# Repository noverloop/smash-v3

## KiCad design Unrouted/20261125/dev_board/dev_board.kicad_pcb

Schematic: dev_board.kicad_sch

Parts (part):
CBAT1_1, CBAT1_2, CBAT1_3, CBAT1_4, CBAT2_1, CBAT2_2, CBAT2_3, CBAT2_4: 22uF; Capacitor_SMD_C_0805_2012Metric; MPN GRM21BR61A226ME51L
CBAT3: 1uF; Capacitor_SMD_C_0603_1608Metric; MPN C0603C105K3RACTU
CMAIN_HOLD1: 100nF; Capacitor_SMD_C_0402_1005Metric; MPN GRM155R71C104KA88D
COUT1_1, COUT1_2: 10uF; Capacitor_SMD_C_0603_1608Metric; MPN CL10A106KP8NNNC
COUT3: 100nF; Capacitor_SMD_C_0402_1005Metric; MPN GRM155R71C104KA88D
C_ACTIVATE_COMP1: 220nF; Capacitor_SMD_C_0603_1608Metric; MPN C0603C224K5RACTU
C_ACTIVATE_IN_1, C_ACTIVATE_IN_2, C_ACTIVATE_IN_3, C_ACTIVATE_IN_4, C_ACTIVATE_IN_5: 2.2uF; Capacitor_SMD_C_0603_1608Metric; MPN C0603C225K8RACTU
C_ACTIVATE_OUT_1, C_ACTIVATE_OUT_2, C_ACTIVATE_OUT_3: 4.7uF; Capacitor_SMD_C_1206_3216Metric; MPN GRM31CC72A475KE11L
C_ACTIVATE_SS1: 47nF; Capacitor_SMD_C_0402_1005Metric; MPN GRM155R71E473KA88D
C_ANTSW_S1_VDD1: 100nF; Capacitor_SMD_C_0402_1005Metric; MPN GRM155R71C104KA88D
C_ANT_S1_DCBLK1, C_ANT_S4_MATCH1: 0.8pF; Capacitor_SMD_C_0402_1005Metric; MPN GJM1555C1HR80BB01D
C_ANT_S1_SHUNT1: 0.5pF; Capacitor_SMD_C_0402_1005Metric; MPN GJM1555C1HR50BB01D
C_AON_IN1: 1uF; Capacitor_SMD_C_0603_1608Metric; MPN C0603C105K3RACTU
C_AON_OUT1: 1uF; Capacitor_SMD_C_0603_1608Metric; MPN C0603C105K3RACTU
C_AWR12_FF1, C_AWR13_FF1, C_AWR18_FF1: 120pF; Capacitor_SMD_C_0402_1005Metric; MPN 04025A121JAT2A
C_AWR_1V2_1_1, C_AWR_1V2_1_2, C_AWR_1V3_1_1, C_AWR_1V3_1_2, C_AWR_1V3_PF_1, C_AWR_1V3_PF_2, C_AWR_1V8_1_1, C_AWR_1V8_1_2, C_AWR_1V8_PF_1, C_AWR_1V8_PF_2: 10uF; Capacitor_SMD_C_0603_1608Metric; MPN CL10A106KP8NNNC
C_AWR_1V2_2, C_AWR_1V3_2, C_AWR_1V8_2: 100nF; Capacitor_SMD_C_0402_1005Metric; MPN GRM155R71C104KA88D
C_AWR_14APLL1, C_AWR_14SYNTH1: 1uF; Capacitor_SMD_C_0603_1608Metric; MPN C0603C105K3RACTU
C_AWR_BUCK_IN1_1, C_AWR_BUCK_IN1_2, C_AWR_BUCK_IN1_3, C_AWR_BUCK_IN1_4, C_AWR_BUCK_IN1_5, C_AWR_BUCK_IN3_1, C_AWR_BUCK_IN3_2, C_AWR_BUCK_IN3_3, C_AWR_BUCK_IN3_4, C_AWR_BUCK_IN3_5: 2.2uF; Capacitor_SMD_C_0603_1608Metric; MPN C0603C225K8RACTU
C_AWR_BUCK_IN2: 100nF; Capacitor_SMD_C_0402_1005Metric; MPN GRM155R71C104KA88D
C_AWR_FLASH_VCC1: 100nF; Capacitor_SMD_C_0402_1005Metric; MPN GRM155R71C104KA88D
C_AWR_NRST1: 100nF; Capacitor_SMD_C_0402_1005Metric; MPN GRM155R71C104KA88D
C_AWR_OSC_VDD1: 100nF; Capacitor_SMD_C_0402_1005Metric; MPN GRM155R71C104KA88D
C_AWR_VBGAP1: 220nF; Capacitor_SMD_C_0603_1608Metric; MPN C0603C224K5RACTU
C_AWR_VIOIN1, C_AWR_VIOIN2: 100nF; Capacitor_SMD_C_0402_1005Metric; MPN GRM155R71C104KA88D
C_AWR_VOUT_PA1: 220nF; Capacitor_SMD_C_0603_1608Metric; MPN C0603C224K5RACTU
C_AWR_VOUT_PA_BULK_1, C_AWR_VOUT_PA_BULK_2, C_AWR_VOUT_PA_BULK_3, C_AWR_VOUT_PA_BULK_4, C_AWR_VOUT_PA_BULK_5: 2.2uF; Capacitor_SMD_C_0603_1608Metric; MPN C0603C225K8RACTU
C_BAT_BULK1, C_BAT_BULK2, C_BAT_BULK3, C_BAT_BULK4, C_BAT_BULK5, C_BAT_BULK6: 22uF; Capacitor_SMD_C_0805_2012Metric; MPN GRM21BR61A226ME51L
C_BAT_SENSE1: 100nF; Capacitor_SMD_C_0402_1005Metric; MPN GRM155R71C104KA88D
C_BLE_DCBLK1: 100pF; Capacitor_SMD_C_0402_1005Metric; MPN 04025A101JAT2A
C_BOOST_CAP1: 100nF; Capacitor_SMD_C_0402_1005Metric; MPN GRM155R71C104KA88D
C_BOOST_COMP1: 1.5nF; Capacitor_SMD_C_0402_1005Metric; MPN C0402C152K3RACTU
C_BOOST_COMP_F1: 390pF; Capacitor_SMD_C_0603_1608Metric; MPN C0603C391J5GACTU
C_BOOST_IN_1, C_BOOST_IN_2, C_BOOST_IN_3, C_BOOST_IN_4, C_BOOST_IN_5: 2.2uF; Capacitor_SMD_C_0603_1608Metric; MPN C0603C225K8RACTU
C_BOOST_OUT1_1, C_BOOST_OUT1_2: 22uF; Capacitor_SMD_C_0805_2012Metric; MPN GRM21BR61E226ME44L
C_BOOST_OUT2_1, C_BOOST_OUT2_2, C_BOOST_OUT2_3, C_BOOST_OUT2_4, C_BOOST_OUT2_5: 2.2uF; Capacitor_SMD_C_0603_1608Metric; MPN C0603C225K8RACTU
C_BOOST_OUT3: 100nF; Capacitor_SMD_C_0402_1005Metric; MPN GRM155R71C104KA88D
C_BOOST_PL1: 47pF; Capacitor_SMD_C_0402_1005Metric; MPN C0402C470J5GACTU
C_BOOST_VCC_1, C_BOOST_VCC_2: 2.2uF; Capacitor_SMD_C_0603_1608Metric; MPN C0603C225K8RACTU
C_CAM_BUCK_IN1: 10uF/LV; Capacitor_SMD_C_0603_1608Metric; MPN CL10A106KP8NNNC
C_CAM_BUCK_OUT_1, C_CAM_BUCK_OUT_2: 10uF; Capacitor_SMD_C_0603_1608Metric; MPN CL10A106KP8NNNC
C_CAM_CPNEG1: 10uF/LV; Capacitor_SMD_C_0603_1608Metric; MPN CL10A106KP8NNNC
C_CAM_CPPOS1: 1uF; Capacitor_SMD_C_0603_1608Metric; MPN C0603C105K3RACTU
C_CAM_EXTCLK_VDD1: 100nF; Capacitor_SMD_C_0402_1005Metric; MPN GRM155R71C104KA88D
C_CAM_LDO2V4: 470nF; Capacitor_SMD_C_0603_1608Metric; MPN C0603C474K3RACTU
C_CAM_LDO_VAA_IN1: 1uF; Capacitor_SMD_C_0603_1608Metric; MPN C0603C105K3RACTU
C_CAM_LDO_VAA_OUT_1, C_CAM_LDO_VAA_OUT_2: 2.2uF; Capacitor_SMD_C_0603_1608Metric; MPN C0603C225K8RACTU
C_CAM_VAA_1: 100nF; Capacitor_SMD_C_0402_1005Metric; MPN GRM155R71C104KA88D
C_CAM_VAA_BULK1: 10uF/LV; Capacitor_SMD_C_0603_1608Metric; MPN CL10A106KP8NNNC
C_CAM_VCORE_1: 470nF; Capacitor_SMD_C_0603_1608Metric; MPN C0603C474K3RACTU
C_CAM_VCORE_BULK1: 10uF/LV; Capacitor_SMD_C_0603_1608Metric; MPN CL10A106KP8NNNC
C_CAM_VCORE_FF1: 120pF; Capacitor_SMD_C_0402_1005Metric; MPN 04025A121JAT2A
C_CAM_VDDIO_1: 1uF; Capacitor_SMD_C_0603_1608Metric; MPN C0603C105K3RACTU
C_CAM_VRT_1, C_CAM_VRT_2: 2.2uF; Capacitor_SMD_C_0603_1608Metric; MPN C0603C225K8RACTU
C_CAN_GW1: 100nF; Capacitor_SMD_C_0402_1005Metric; MPN GRM155R71C104KA88D
C_CAN_GW_VIO1: 100nF; Capacitor_SMD_C_0402_1005Metric; MPN GRM155R71C104KA88D
C_COMP_PZ1: 100nF; Capacitor_SMD_C_0402_1005Metric; MPN GRM155R71C104KA88D
C_DDR_BULK1_1, C_DDR_BULK1_2, C_DDR_BULK1_3, C_DDR_BULK1_4, C_DDR_BULK1_5, C_DDR_BULK2_1, C_DDR_BULK2_2, C_DDR_BULK2_3, C_DDR_BULK2_4, C_DDR_BULK2_5: 2.2uF; Capacitor_SMD_C_0603_1608Metric; MPN C0603C225K8RACTU
C_DDR_VDD1, C_DDR_VDD2, C_DDR_VDD3, C_DDR_VDD4, C_DDR_VDD5, C_DDR_VDD6: 100nF; Capacitor_SMD_C_0402_1005Metric; MPN GRM155R71C104KA88D
C_DDR_VREFCA1: 100nF; Capacitor_SMD_C_0402_1005Metric; MPN GRM155R71C104KA88D
C_DDR_VREFDQ1: 100nF; Capacitor_SMD_C_0402_1005Metric; MPN GRM155R71C104KA88D
C_DEV_BENCH1: 47uF; Capacitor_Tantalum_SMD_CP_EIA-7343-15_Kemet-W; MPN T528W 47uF (7343-15 thinnest variant)
C_DEV_BUSSW0, C_DEV_BUSSW1, C_DEV_BUSSW2, C_DEV_BUSSW3: 100nF; Capacitor_SMD_C_0402_1005Metric; MPN GRM155R71C104KA88D
C_DEV_CAN_VCC1: 100nF; Capacitor_SMD_C_0402_1005Metric; MPN GRM155R71C104KA88D
C_DEV_CAN_VIO1: 100nF; Capacitor_SMD_C_0402_1005Metric; MPN GRM155R71C104KA88D
C_DEV_FLATSW0, C_DEV_FLATSW1, C_DEV_FLATSW2, C_DEV_FLATSW3: 100nF; Capacitor_SMD_C_0402_1005Metric; MPN GRM155R71C104KA88D
C_DEV_FLAT_PWR_SS1: 22nF; Capacitor_SMD_C_0402_1005Metric; MPN C0402C223K3RACTU
C_DEV_INA1: 100nF; Capacitor_SMD_C_0402_1005Metric; MPN GRM155R71C104KA88D
C_DEV_ISENSE1: 100nF; Capacitor_SMD_C_0402_1005Metric; MPN GRM155R71C104KA88D
C_DEV_LDO_IN1: 1uF; Capacitor_SMD_C_0603_1608Metric; MPN C0603C105K3RACTU
C_DEV_LDO_OUT_1, C_DEV_LDO_OUT_2, C_DEV_LDO_OUT_3, C_DEV_LDO_OUT_4, C_DEV_LDO_OUT_5: 2.2uF; Capacitor_SMD_C_0603_1608Metric; MPN C0603C225K8RACTU
C_DEV_MCU_0, C_DEV_MCU_1, C_DEV_MCU_2, C_DEV_MCU_3: 100nF; Capacitor_SMD_C_0402_1005Metric; MPN GRM155R71C104KA88D
C_DEV_MCU_BULK_1, C_DEV_MCU_BULK_2: 2.2uF; Capacitor_SMD_C_0603_1608Metric; MPN C0603C225K8RACTU
C_DEV_MCU_NRST1: 100nF; Capacitor_SMD_C_0402_1005Metric; MPN GRM155R71C104KA88D
C_DEV_MCU_VCAP_1, C_DEV_MCU_VCAP_2: 2.2uF; Capacitor_SMD_C_0603_1608Metric; MPN C0603C225K8RACTU
C_DEV_MON1_0, C_DEV_MON1_1, C_DEV_MON1_2, C_DEV_MON1_3, C_DEV_MON1_4, C_DEV_MON1_5, C_DEV_MON1_6, C_DEV_MON1_7, C_DEV_MON2_0, C_DEV_MON2_1, C_DEV_MON2_2, C_DEV_MON2_3, C_DEV_MON2_4, C_DEV_MON2_5, C_DEV_MON2_6, C_DEV_MON2_7, C_DEV_MON3_0, C_DEV_MON3_1, C_DEV_MON3_2, C_DEV_MON3_3, C_DEV_MON3_4: 10nF; Capacitor_SMD_C_0402_1005Metric; MPN C0402C103K3RACTU
C_DEV_MON1_AVDD1, C_DEV_MON1_DECAP1, C_DEV_MON1_DVDD1, C_DEV_MON2_AVDD1, C_DEV_MON2_DECAP1, C_DEV_MON2_DVDD1, C_DEV_MON3_AVDD1, C_DEV_MON3_DECAP1, C_DEV_MON3_DVDD1: 1uF; Capacitor_SMD_C_0603_1608Metric; MPN C0603C105K3RACTU
C_DEV_OVP_FLAT_IN1: 1nF; Capacitor_SMD_C_0402_1005Metric; MPN C0402C102K3RACTU
C_DEV_OVP_FLAT_VCC1: 100nF; Capacitor_SMD_C_0402_1005Metric; MPN GRM155R71C104KA88D
C_DEV_OVP_IN1: 1nF; Capacitor_SMD_C_0402_1005Metric; MPN C0402C102K3RACTU
C_DEV_OVP_VCC1: 100nF; Capacitor_SMD_C_0402_1005Metric; MPN GRM155R71C104KA88D
C_DEV_TWR_PWR_SS1: 22nF; Capacitor_SMD_C_0402_1005Metric; MPN C0402C223K3RACTU
C_FIN1_VM1, C_FIN2_VM1, C_FIN3_VM1, C_FIN4_VM1: 100nF; Capacitor_SMD_C_0402_1005Metric; MPN GRM155R71C104KA88D
C_FIN_MCU_BULK1: 1uF; Capacitor_SMD_C_0603_1608Metric; MPN C0603C105K3RACTU
C_FIN_MCU_NRST1: 100nF; Capacitor_SMD_C_0402_1005Metric; MPN GRM155R71C104KA88D
C_FIN_MCU_SMPS_IN_1, C_FIN_MCU_SMPS_IN_2: 2.2uF; Capacitor_SMD_C_0603_1608Metric; MPN C0603C225K8RACTU
C_FIN_MCU_VDD1, C_FIN_MCU_VDD2: 100nF; Capacitor_SMD_C_0402_1005Metric; MPN GRM155R71C104KA88D
C_FIN_MCU_VDD11_1, C_FIN_MCU_VDD11_2: 2.2uF; Capacitor_SMD_C_0603_1608Metric; MPN C0603C225K8RACTU
C_FIN_MCU_VDDA1: 100nF; Capacitor_SMD_C_0402_1005Metric; MPN GRM155R71C104KA88D
C_FIN_VM_BULK_1, C_FIN_VM_BULK_2, C_FIN_VM_BULK_3, C_FIN_VM_BULK_4, C_FIN_VM_BULK_5: 2.2uF; Capacitor_SMD_C_0603_1608Metric; MPN C0603C225K8RACTU
C_HACC1: 100nF; Capacitor_SMD_C_0402_1005Metric; MPN GRM155R71C104KA88D
C_HACC2_1, C_HACC2_2, C_HACC2_3, C_HACC2_4, C_HACC2_5: 2.2uF; Capacitor_SMD_C_0603_1608Metric; MPN C0603C225K8RACTU
C_HEALTH_COIL_1, C_HEALTH_COIL_2, C_HEALTH_COIL_3, C_HEALTH_COIL_4, C_HEALTH_COIL_5: 2.2uF; Capacitor_SMD_C_0603_1608Metric; MPN C0603C225K8RACTU
C_IMU1_1, C_IMU2_1, C_IMU3_1: 100nF; Capacitor_SMD_C_0402_1005Metric; MPN GRM155R71C104KA88D
C_IMU1_2, C_IMU2_2, C_IMU3_2: 2.2uF; Capacitor_SMD_C_0603_1608Metric; MPN C0603C225K8RACTU
C_IMU1_3, C_IMU2_3, C_IMU3_3: 10nF; Capacitor_SMD_C_0402_1005Metric; MPN C0402C103K3RACTU
C_IR_TX1: 1uF; Capacitor_SMD_C_0603_1608Metric; MPN C0603C105K3RACTU
C_IR_TX_C1: 1uF; Capacitor_SMD_C_0603_1608Metric; MPN C0603C105K3RACTU
C_IR_TX_Q1: 1uF; Capacitor_SMD_C_0603_1608Metric; MPN C0603C105K3RACTU
C_IR_WAKE1: 10nF; Capacitor_SMD_C_0402_1005Metric; MPN C0402C103K3RACTU
C_J_HALL_FIN_VCC1: 100nF; Capacitor_SMD_C_0402_1005Metric; MPN GRM155R71C104KA88D
C_LR_BULK_1, C_LR_BULK_2: 2.2uF; Capacitor_SMD_C_0603_1608Metric; MPN C0603C225K8RACTU
C_LR_DTC1_VDD1, C_LR_DTC2_VDD1: 100nF; Capacitor_SMD_C_0402_1005Metric; MPN GRM155R71C104KA88D
C_LR_HF_ANTBLK1: 100pF; Capacitor_SMD_C_0402_1005Metric; MPN 04025A101JAT2A
C_LR_HF_RX1: 0.8pF; Capacitor_SMD_C_0402_1005Metric; MPN GJM1555C1HR80BB01D
C_LR_HF_RXBLK1: 100pF; Capacitor_SMD_C_0402_1005Metric; MPN 04025A101JAT2A
C_LR_HF_TX1: 1.2pF; Capacitor_SMD_C_0402_1005Metric; MPN GJM1555C1H1R2BB01D
C_LR_HF_TX2: 1.0pF; Capacitor_SMD_C_0402_1005Metric; MPN GJM1555C1H1R0BB01D
C_LR_HF_TXBLK1: 100pF; Capacitor_SMD_C_0402_1005Metric; MPN 04025A101JAT2A
C_LR_IFSW_VDD1: 100nF; Capacitor_SMD_C_0402_1005Metric; MPN GRM155R71C104KA88D
C_LR_SW_HF_VDD1: 100nF; Capacitor_SMD_C_0402_1005Metric; MPN GRM155R71C104KA88D
C_LR_TCXO_AC1: 10pF; Capacitor_SMD_C_0402_1005Metric; MPN 04025A100JAT2A
C_LR_TCXO_MEMS1: 100nF; Capacitor_SMD_C_0402_1005Metric; MPN GRM155R71C104KA88D
C_LR_TCXO_MEMS2: 1uF; Capacitor_SMD_C_0603_1608Metric; MPN C0603C105K3RACTU
C_LR_VBAT1: 100nF; Capacitor_SMD_C_0402_1005Metric; MPN GRM155R71C104KA88D
C_LR_VDCC1, C_LR_VDCC2: 1uF; Capacitor_SMD_C_0603_1608Metric; MPN C0603C105K3RACTU
C_LR_VPAX1, C_LR_VPAX2: 2.2uF; Capacitor_SMD_C_0603_1608Metric; MPN C0603C225K8RACTU
C_LR_VRPA1: 1nF; Capacitor_SMD_C_0402_1005Metric; MPN C0402C102K3RACTU
C_LR_VTCXO1: 100nF; Capacitor_SMD_C_0402_1005Metric; MPN GRM155R71C104KA88D
C_MAG1: 100nF; Capacitor_SMD_C_0402_1005Metric; MPN GRM155R71C104KA88D
C_MAG2: 1uF; Capacitor_SMD_C_0603_1608Metric; MPN C0603C105K3RACTU
C_MAG_C1: 2.2uF; Capacitor_SMD_C_0603_1608Metric; MPN C0603C225K8RACTU
C_MAG_LDO_IN1: 1uF; Capacitor_SMD_C_0603_1608Metric; MPN C0603C105K3RACTU
C_MAG_LDO_OUT1: 1uF; Capacitor_SMD_C_0603_1608Metric; MPN C0603C105K3RACTU
C_MAG_SHELF1: 100nF; Capacitor_SMD_C_0402_1005Metric; MPN GRM155R71C104KA88D
C_MAG_WAKE1: 100nF; Capacitor_SMD_C_0402_1005Metric; MPN GRM155R71C104KA88D
C_MPU_0V82_1, C_MPU_0V82_2, C_MPU_5V2, C_MPU_18AON1, C_MPU_18A_1, C_MPU_18A_2, C_MPU_33b1: 100nF; Capacitor_SMD_C_0402_1005Metric; MPN GRM155R71C104KA88D
C_MPU_0V82_BULK1, C_MPU_5V_1, C_MPU_5V_2, C_MPU_5V_3, C_MPU_5V_4, C_MPU_5V_5, C_MPU_33_1, C_MPU_33_2, C_MPU_33_3, C_MPU_33_4, C_MPU_33_5: 2.2uF; Capacitor_SMD_C_0603_1608Metric; MPN C0603C225K8RACTU
C_MPU_HSE_VDD1: 100nF; Capacitor_SMD_C_0402_1005Metric; MPN GRM155R71C104KA88D
C_MPU_LSE_VDD1: 100nF; Capacitor_SMD_C_0402_1005Metric; MPN GRM155R71C104KA88D
C_MPU_NRST1: 100nF; Capacitor_SMD_C_0402_1005Metric; MPN GRM155R71C104KA88D
C_MPU_QDDR_1, C_MPU_QDDR_2: 100nF; Capacitor_SMD_C_0402_1005Metric; MPN GRM155R71C104KA88D
C_MPU_V08CAP1: 2.2uF; Capacitor_SMD_C_0603_1608Metric; MPN C0603C225K8RACTU
C_NAND_A_BULK1: 1uF; Capacitor_SMD_C_0603_1608Metric; MPN C0603C105K3RACTU
C_NAND_A_VCC1: 100nF; Capacitor_SMD_C_0402_1005Metric; MPN GRM155R71C104KA88D
C_NAND_B_BULK1: 1uF; Capacitor_SMD_C_0603_1608Metric; MPN C0603C105K3RACTU
C_NAND_B_VCC1: 100nF; Capacitor_SMD_C_0402_1005Metric; MPN GRM155R71C104KA88D
C_PMIC_0V9_1_1, C_PMIC_0V9_1_2, C_PMIC_0V82_1_1, C_PMIC_0V82_1_2, C_PMIC_1V8_1_1, C_PMIC_1V8_1_2, C_PMIC_3V3_1_1, C_PMIC_3V3_1_2: 10uF; Capacitor_SMD_C_0603_1608Metric; MPN CL10A106KP8NNNC
C_PMIC_0V9_2, C_PMIC_0V82_2, C_PMIC_1V8_2, C_PMIC_1V35_2, C_PMIC_2V8_2, C_PMIC_3V3_2: 100nF; Capacitor_SMD_C_0402_1005Metric; MPN GRM155R71C104KA88D
C_PMIC_1V35_1_1, C_PMIC_1V35_1_2, C_PMIC_1V35_1_3, C_PMIC_1V35_1_4, C_PMIC_1V35_1_5, C_PMIC_2V8_1_1, C_PMIC_2V8_1_2, C_PMIC_5V_FILT_1, C_PMIC_5V_FILT_2, C_PMIC_5V_FILT_3, C_PMIC_5V_FILT_4, C_PMIC_5V_FILT_5: 2.2uF; Capacitor_SMD_C_0603_1608Metric; MPN C0603C225K8RACTU
C_PMIC_INTLDO_1, C_PMIC_INTLDO_2: 2.2uF; Capacitor_SMD_C_0603_1608Metric; MPN C0603C225K8RACTU
C_PMIC_LDO1_1, C_PMIC_LDO1_2, C_PMIC_LDO2_1, C_PMIC_LDO2_2, C_PMIC_LDO4_1, C_PMIC_LDO4_2: 2.2uF; Capacitor_SMD_C_0603_1608Metric; MPN C0603C225K8RACTU
C_PMIC_LDO6, C_PMIC_LDO7, C_PMIC_LDO8: 100nF; Capacitor_SMD_C_0402_1005Metric; MPN GRM155R71C104KA88D
C_PMIC_VIN1: 22uF; Capacitor_Tantalum_SMD_CP_EIA-3528-12_Kemet-T; MPN T491T226K010AT
C_PMIC_VIN2: 100nF; Capacitor_SMD_C_0402_1005Metric; MPN GRM155R71C104KA88D
C_PMIC_VIN3, C_PMIC_VIN4, C_PMIC_VIN5, C_PMIC_VIN6: 2.2uF; Capacitor_SMD_C_0603_1608Metric; MPN C0603C225K8RACTU
C_PMIC_VREFDDR1: 1uF; Capacitor_SMD_C_0402_1005Metric; MPN GRM155R61E105KA12D
C_PWR_FF1: 120pF; Capacitor_SMD_C_0402_1005Metric; MPN 04025A121JAT2A
C_PWR_IN_1, C_PWR_IN_2, C_PWR_IN_3, C_PWR_IN_4, C_PWR_IN_5: 2.2uF; Capacitor_SMD_C_0603_1608Metric; MPN C0603C225K8RACTU
C_PZ_TX1: 10nF; Capacitor_SMD_C_0402_1005Metric; MPN C0402C103K3RACTU
C_QPD_VREF1: 1uF; Capacitor_SMD_C_0603_1608Metric; MPN C0603C105K3RACTU
C_QPD_VREF2: 100nF; Capacitor_SMD_C_0402_1005Metric; MPN GRM155R71C104KA88D
C_TIA_A1: 8.2pF; Capacitor_SMD_C_0603_1608Metric; MPN C0603C829C5GACTU
C_TIA_A_PWR1: 100nF; Capacitor_SMD_C_0402_1005Metric; MPN GRM155R71C104KA88D
C_TIA_B1: 8.2pF; Capacitor_SMD_C_0603_1608Metric; MPN C0603C829C5GACTU
C_TIA_B_PWR1: 100nF; Capacitor_SMD_C_0402_1005Metric; MPN GRM155R71C104KA88D
C_TIA_C1: 8.2pF; Capacitor_SMD_C_0603_1608Metric; MPN C0603C829C5GACTU
C_TIA_C_PWR1: 100nF; Capacitor_SMD_C_0402_1005Metric; MPN GRM155R71C104KA88D
C_TIA_D1: 8.2pF; Capacitor_SMD_C_0603_1608Metric; MPN C0603C829C5GACTU
C_TIA_D_PWR1: 100nF; Capacitor_SMD_C_0402_1005Metric; MPN GRM155R71C104KA88D
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
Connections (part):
3V3: COUT1_1.1, COUT1_2.1, COUT3.1, C_PWR_FF1.1, C_TMP1.1, J_CAST_power_board1.3 (3V3@27.068deg), L_PWR1.2, R_DEV_MON2_2.1, R_DEV_SH_3V3_ACT1.2, R_DEV_SH_3V3_QPD1.2, R_DEV_SH_3V3_RADAR1.2, R_DEV_SH_3V3_WAKE1.2, R_PWR_FB1.1, S_DEV_LAUNCH1.2 (A), TP_DEV_SH_3V3_ACT_B1.1, TP_DEV_SH_3V3_QPD_B1.1, TP_DEV_SH_3V3_RADAR_B1.1, TP_DEV_SH_3V3_WAKE_B1.1, U_PMIC1.29 (VIO), U_TMP1.6 (A1), U_TMP1.8 (VDD)
3V3_AON: C_AON_OUT1.1, C_COMP_PZ1.1, C_MAG_WAKE1.1, C_WBA_BULK_1.1, C_WBA_BULK_2.1, C_WBA_BULK_3.1, C_WBA_BULK_4.1, C_WBA_BULK_5.1, C_WBA_SMPS_IN_1.1, C_WBA_SMPS_IN_2.1, C_WBA_SMPS_IN_3.1, C_WBA_SMPS_IN_4.1, C_WBA_SMPS_IN_5.1, C_WBA_VDD1.1, C_WBA_VDD2.1, C_WBA_VDD3.1, C_WBA_VDD4.1, C_WBA_VDDA1.1, C_WBA_VDDANA1.1, C_WBA_VDDA_1U1.1, C_WBA_VDDRF1.1, C_WBA_VDDRFPA1.1, C_WBA_VDDSMPS1.1, J_CAST_activation_interface1.22 (3V3_AON@78.496deg), J_CAST_aft_end_board1.12 (3V3_AON@78.25deg), J_CAST_wakeup_board1.15 (3V3_AON@78.496deg), RPU_IR_WAKE1.1, RPU_MAG_WAKE1.1, R_DEV_MON2_3.1, R_VDD_SENSE1.2, R_WBA_NRST1.1, U_AON_LDO1.1 (VOUT), U_COMP_PZ1.B1 (VCC), U_MAG_WAKE1.1 (VCC), U_WBA1.A4 (VDD_RFPA), U_WBA1.A6 (VDDRF), U_WBA1.B1 (VDD_SMPS), U_WBA1.B6 (VDD_ANA), U_WBA1.C6 (VDD_1), U_WBA1.D5 (VDD_2), U_WBA1.E4 (VDD_3), U_WBA1.F1 (VDDA), U_WBA1.F5 (VDD_4)
3V3__ACT: C_FIN_MCU_BULK1.1, C_FIN_MCU_SMPS_IN_1.1, C_FIN_MCU_SMPS_IN_2.1, C_FIN_MCU_VDD1.1, C_FIN_MCU_VDD2.1, C_FIN_MCU_VDDA1.1, C_HACC1.1, C_HACC2_1.1, C_HACC2_2.1, C_HACC2_3.1, C_HACC2_4.1, C_HACC2_5.1, C_IMU1_1.1, C_IMU1_2.1, C_IMU1_3.1, C_IMU2_1.1, C_IMU2_2.1, C_IMU2_3.1, C_IMU3_1.1, C_IMU3_2.1, C_IMU3_3.1, C_J_HALL_FIN_VCC1.1, C_MAG2.1, C_MAG_LDO_IN1.1, J_CAST_activation_interface1.5 (3V3@27.068deg), J_HALL_FIN_VCC1.1, R_DEV_SH_3V3_ACT1.1, R_FIN_MCU_NRST1.1, R_FIN_SPI_CS_PU1.1, R_HALL_VIN1.1, R_IMU1_SCX_PU1.1, R_IMU1_SDX_PU1.1, R_IMU2_SCX_PU1.1, R_IMU2_SDX_PU1.1, R_IMU3_SCX_PU1.1, R_IMU3_SDX_PU1.1, R_J_HALL_FIN_PU1.1, TP_DEV_SH_3V3_ACT_T1.1, U_FIN1.16 (MODE), U_FIN2.16 (MODE), U_FIN3.16 (MODE), U_FIN4.16 (MODE), U_FIN_MCU1.A1 (VDD_1), U_FIN_MCU1.A8 (VDD_2), U_FIN_MCU1.B1 (VBAT), U_FIN_MCU1.B8 (VDDUSB), U_FIN_MCU1.G1 (VDDA), U_FIN_MCU1.H1 (VDD_3), U_FIN_MCU1.H6 (VDDSMPS), U_FIN_MCU1.H8 (VDD_4), U_HACC1.1 (VDD_IO), U_HACC1.8 (CS), U_HACC1.14 (VDD), U_HACC1.15 (RESERVED_2), U_IMU1.5 (VDDIO), U_IMU1.8 (VDD), U_IMU1.12 (CS), U_IMU2.5 (VDDIO), U_IMU2.8 (VDD), U_IMU2.12 (CS), U_IMU3.1 (SDO/SA0), U_IMU3.5 (VDDIO), U_IMU3.8 (VDD), U_IMU3.12 (CS), U_MAG1.B3 (VDDIO), U_MAG_LDO1.3 (ON/OFF), U_MAG_LDO1.4 (VIN)
3V3__QPD: C_TIA_A_PWR1.1, C_TIA_B_PWR1.1, C_TIA_C_PWR1.1, C_TIA_D_PWR1.1, J_CAST_qpd_module1.2 (3V3@27.068deg), R_DEV_SH_3V3_QPD1.1, R_QPD_VREF_H1.1, TP_DEV_SH_3V3_QPD_T1.1, U_TIA_A1.5 (V+), U_TIA_B1.5 (V+), U_TIA_C1.5 (V+), U_TIA_D1.5 (V+)
3V3__RADAR: J_CAST_radar_module1.3 (3V3@27.068deg), R_DEV_SH_3V3_RADAR1.1, TP_DEV_SH_3V3_RADAR_T1.1
3V3__WAKE: C_ANTSW_S1_VDD1.1, C_LR_DTC1_VDD1.1, C_LR_DTC2_VDD1.1, C_LR_IFSW_VDD1.1, C_LR_SW_HF_VDD1.1, C_WBA_HSE_VDD1.1, C_XV_MIX_VCC1.1, C_XV_MIX_VCC2.1, C_XV_TR1_VDD1.1, C_XV_TR2_VDD1.1, FB_LR_VBAT1.1, FB_XV_LO1.1, J_CAST_wakeup_board1.3 (3V3@27.068deg), Q_LR_TCXO_SW1.2 (S), RPU_I2C2_SCL1.1, RPU_I2C2_SDA1.1, RPU_I2C3_SCL1.1, RPU_I2C3_SDA1.1, RPU_SCL_EXT1.1, RPU_SDA_EXT1.1, R_DEV_SH_3V3_WAKE1.1, R_LR_NSS_PU1.1, R_LR_TCXO_SW_PU1.1, R_XV_LNA_VDD1.1, TP_3V3.1, TP_DEV_SH_3V3_WAKE_T1.1, U_ANTSW_S1.4 (VDD), U_LR_DTC1.4 (VDD), U_LR_DTC2.4 (VDD), U_LR_IFSW1.4 (VDD), U_LR_SW_HF1.4 (VDD), U_XV_MIX1.9 (VCC), U_XV_TR1.4 (VDD), U_XV_TR2.4 (VDD), Y_WBA_HSE1.1 (STANDBY#), Y_WBA_HSE1.4 (VDD)
ACTIVATE_BOOST_EN: J_CAST_companion_compute1.60 (ACTIVATE_BOOST_EN@273.383deg), J_CAST_power_board1.27 (ACTIVATE_BOOST_EN@273.383deg), R_ACTIVATE_EN_PD1.1, TP_DEV_DBG_ACTIVATE_BOOST_EN1.1, U_ACTIVATE_BOOST1.4 (EN), U_MPU1.F5 (PG10)
ACTIVATE_COMP: R_ACTIVATE_COMP1.1, U_ACTIVATE_BOOST1.8 (COMP)
ACTIVATE_COMP_C: C_ACTIVATE_COMP1.1, R_ACTIVATE_COMP1.2
ACTIVATE_CONFIRM: J_CAST_activation_interface1.62 (ACTIVATE_CONFIRM@322.105deg), J_CAST_companion_compute1.70 (ACTIVATE_CONFIRM@322.105deg), R_ACTIVATE_MON1.2, R_ACTIVATE_MON2.1, R_ACT_CONFIRM_PAD1.2, U_MPU1.C10 (PD9)
ACTIVATE_CONFIRM_PAD: J_CAST_activation_interface1.56 (ACTIVATE_CONFIRM_PAD@305.865deg), J_CAST_aft_end_board1.31 (ACTIVATE_CONFIRM_PAD@264.25deg), R_ACT_CONFIRM_PAD1.1, TP_ACT_CONFIRM1.1, U_ESD_AFT7.3 (IO2)
ACTIVATE_FB: R_ACTIVATE_FB1.2, R_ACTIVATE_FB2.1, U_ACTIVATE_BOOST1.9 (FB)
ACTIVATE_FREQ: R_ACTIVATE_FREQ1.1, U_ACTIVATE_BOOST1.10 (FREQ)
ACTIVATE_HV: C_ACTIVATE_OUT_1.1, C_ACTIVATE_OUT_2.1, C_ACTIVATE_OUT_3.1, D_ACTIVATE1.1 (K), J_CAST_activation_interface1.55 (ACTIVATE_HV@303.158deg), J_CAST_power_board1.31 (ACTIVATE_HV@303.158deg), Q_PARACHUTE_CUTTER_ACTIVATE1.4 (S_1), Q_PARACHUTE_CUTTER_ACTIVATE1.8 (S_2), R_ACTIVATE_BLEED1.1, R_ACTIVATE_FB1.1, R_ACTIVATE_MON1.1, R_DEV_LED_HV1.1, R_DEV_MON2_6.1, R_PARACHUTE_CUTTER_ACTIVATE_H1.1, TP_DEV_DBG_ACTIVATE_HV1.1
ACTIVATE_SS: C_ACTIVATE_SS1.1, U_ACTIVATE_BOOST1.5 (SS)
ACTIVATE_SW: D_ACTIVATE1.2 (A), L_ACTIVATE1.1, U_ACTIVATE_BOOST1.1 (SW_1), U_ACTIVATE_BOOST1.2 (SW_2)
ACT_COL_0: D_ACT_COL0_TVS1.1 (K), J_CAST_activation_interface1.13 (ACT_COL_0@54.135deg), J_CAST_aft_end_board1.7 (ACT_COL_0@49.25deg), P_ACT_COL_0.1, Q_ACT_COL0.3 (D)
ACT_COL_1: D_ACT_COL1_TVS1.1 (K), J_CAST_activation_interface1.15 (ACT_COL_1@59.549deg), J_CAST_aft_end_board1.8 (ACT_COL_1@52deg), P_ACT_COL_1.1, Q_ACT_COL1.3 (D)
ACT_COL_2: D_ACT_COL2_TVS1.1 (K), J_CAST_activation_interface1.53 (ACT_COL_2@297.744deg), J_CAST_aft_end_board1.30 (ACT_COL_2@261.5deg), P_ACT_COL_2.1, Q_ACT_COL2.3 (D)
ACT_COL_3: D_ACT_COL3_TVS1.1 (K), J_CAST_activation_interface1.16 (ACT_COL_3@62.256deg), J_CAST_aft_end_board1.9 (ACT_COL_3@54.75deg), P_ACT_COL_3.1, Q_ACT_COL3.3 (D)
ACT_COL_SEL_0: Q_ACT_COL0.1 (G), R_ACT_COL0_PD1.1, U_FIN_MCU1.D7 (PA8)
ACT_COL_SEL_1: Q_ACT_COL1.1 (G), R_ACT_COL1_PD1.1, U_FIN_MCU1.D6 (PA9)
ACT_COL_SEL_2: Q_ACT_COL2.1 (G), R_ACT_COL2_PD1.1, U_FIN_MCU1.D5 (PA10)
ACT_COL_SEL_3: Q_ACT_COL3.1 (G), R_ACT_COL3_PD1.1, U_FIN_MCU1.C8 (PA11)
ACT_ROW_0: D_ACT_WIRE_0.2 (A), D_ACT_WIRE_1.2 (A), D_ACT_WIRE_2.2 (A), D_ACT_WIRE_3.2 (A), J_CAST_activation_interface1.52 (ACT_ROW_0@295.038deg), J_CAST_aft_end_board1.29 (ACT_ROW_0@258.75deg), Q_ACT_ROW0.1 (D_1), Q_ACT_ROW0.2 (D_2), Q_ACT_ROW0.5 (D_3), Q_ACT_ROW0.6 (D_4), Q_ACT_ROW0.7 (D_5)
ACT_ROW_0_G: Q_ACT_ROW0.3 (G), R_ACT_ROW0_H1.2, R_ACT_ROW0_L1.1
ACT_ROW_0_GD: Q_ACT_ROW0_LS1.3 (D), R_ACT_ROW0_L1.2
ACT_ROW_1: D_ACT_WIRE_4.2 (A), D_ACT_WIRE_5.2 (A), D_ACT_WIRE_6.2 (A), D_ACT_WIRE_7.2 (A), J_CAST_activation_interface1.17 (ACT_ROW_1@64.962deg), J_CAST_aft_end_board1.10 (ACT_ROW_1@57.5deg), Q_ACT_ROW1.1 (D_1), Q_ACT_ROW1.2 (D_2), Q_ACT_ROW1.5 (D_3), Q_ACT_ROW1.6 (D_4), Q_ACT_ROW1.7 (D_5)
ACT_ROW_1_G: Q_ACT_ROW1.3 (G), R_ACT_ROW1_H1.2, R_ACT_ROW1_L1.1
ACT_ROW_1_GD: Q_ACT_ROW1_LS1.3 (D), R_ACT_ROW1_L1.2
ACT_ROW_2: D_ACT_WIRE_8.2 (A), D_ACT_WIRE_9.2 (A), D_ACT_WIRE_10.2 (A), D_ACT_WIRE_11.2 (A), J_CAST_activation_interface1.51 (ACT_ROW_2@292.331deg), J_CAST_aft_end_board1.28 (ACT_ROW_2@256deg), Q_ACT_ROW2.1 (D_1), Q_ACT_ROW2.2 (D_2), Q_ACT_ROW2.5 (D_3), Q_ACT_ROW2.6 (D_4), Q_ACT_ROW2.7 (D_5)
ACT_ROW_2_G: Q_ACT_ROW2.3 (G), R_ACT_ROW2_H1.2, R_ACT_ROW2_L1.1
ACT_ROW_2_GD: Q_ACT_ROW2_LS1.3 (D), R_ACT_ROW2_L1.2
ACT_ROW_3: D_ACT_WIRE_12.2 (A), D_ACT_WIRE_13.2 (A), D_ACT_WIRE_14.2 (A), D_ACT_WIRE_15.2 (A), J_CAST_activation_interface1.18 (ACT_ROW_3@67.669deg), J_CAST_aft_end_board1.11 (ACT_ROW_3@60.25deg), Q_ACT_ROW3.1 (D_1), Q_ACT_ROW3.2 (D_2), Q_ACT_ROW3.5 (D_3), Q_ACT_ROW3.6 (D_4), Q_ACT_ROW3.7 (D_5)
ACT_ROW_3_G: Q_ACT_ROW3.3 (G), R_ACT_ROW3_H1.2, R_ACT_ROW3_L1.1
ACT_ROW_3_GD: Q_ACT_ROW3_LS1.3 (D), R_ACT_ROW3_L1.2
ACT_ROW_SEL_0: Q_ACT_ROW0_LS1.1 (G), R_ACT_ROW0_PD1.1, U_FIN_MCU1.E2 (PC0)
ACT_ROW_SEL_1: Q_ACT_ROW1_LS1.1 (G), R_ACT_ROW1_PD1.1, U_FIN_MCU1.E3 (PC1)
ACT_ROW_SEL_2: Q_ACT_ROW2_LS1.1 (G), R_ACT_ROW2_PD1.1, U_FIN_MCU1.E4 (PC2)
ACT_ROW_SEL_3: Q_ACT_ROW3_LS1.1 (G), R_ACT_ROW3_PD1.1, U_FIN_MCU1.F2 (PC3)
ACT_WIRE_0: D_ACT_WIRE_0.1 (K), P_ACT_WIRE_0.1
ACT_WIRE_1: D_ACT_WIRE_1.1 (K), P_ACT_WIRE_1.1
ACT_WIRE_2: D_ACT_WIRE_2.1 (K), P_ACT_WIRE_2.1
ACT_WIRE_3: D_ACT_WIRE_3.1 (K), P_ACT_WIRE_3.1
ACT_WIRE_4: D_ACT_WIRE_4.1 (K), P_ACT_WIRE_4.1
ACT_WIRE_5: D_ACT_WIRE_5.1 (K), P_ACT_WIRE_5.1
ACT_WIRE_6: D_ACT_WIRE_6.1 (K), P_ACT_WIRE_6.1
ACT_WIRE_7: D_ACT_WIRE_7.1 (K), P_ACT_WIRE_7.1
ACT_WIRE_8: D_ACT_WIRE_8.1 (K), P_ACT_WIRE_8.1
ACT_WIRE_9: D_ACT_WIRE_9.1 (K), P_ACT_WIRE_9.1
ACT_WIRE_10: D_ACT_WIRE_10.1 (K), P_ACT_WIRE_10.1
ACT_WIRE_11: D_ACT_WIRE_11.1 (K), P_ACT_WIRE_11.1
ACT_WIRE_12: D_ACT_WIRE_12.1 (K), P_ACT_WIRE_12.1
ACT_WIRE_13: D_ACT_WIRE_13.1 (K), P_ACT_WIRE_13.1
ACT_WIRE_14: D_ACT_WIRE_14.1 (K), P_ACT_WIRE_14.1
ACT_WIRE_15: D_ACT_WIRE_15.1 (K), P_ACT_WIRE_15.1
ANTSW_S1_LR: R_ANTSW_S1_PD1.1, U_ANTSW_S1.6 (CTRL), U_LR1.9 (DIO9)
ANT_HF_S1: C_ANT_S1_DCBLK1.2, J_CAST_wakeup_board1.22 (ANT_HF_S1@129.4deg), J_DEV_HF_S1.3
ANT_HF_S4: C_ANT_S4_MATCH1.2, J_CAST_wakeup_board1.25 (ANT_HF_S4@154.3deg), J_DEV_HF_S4.3
ANT_S1_COM: C_ANT_S1_DCBLK1.1, C_ANT_S1_SHUNT1.1, U_ANTSW_S1.5 (RFIN)
AON_EN: DHOLD_AON1.1 (K), DHOLD_AON_MP25.1 (K), Q_AON_EN1.3 (D), R_AON_EN_PD1.1, U_AON_LDO1.3 (ON/OFF)
AON_EN_GATE: D_AON_WAKE1.2 (A), D_AON_WAKE2.2 (A), Q_AON_EN1.1 (G), Q_USB_WAKE2.3 (D), RAON_PU1.2
AWR_1V2: C_AWR12_FF1.1, C_AWR_1V2_1_1.1, C_AWR_1V2_1_2.1, C_AWR_1V2_2.1, J_CAST_radar_module1.42 (AWR_1V2@249.023deg), L_AWR_BUCK12.2, R_AWR12_FB1.1, R_DEV_MON2_7.1, TP_DEV_DBG_AWR_1V2.1, U_AWR1.A5 (VIN_SRAM_1), U_AWR1.C1 (VNWA_1), U_AWR1.E1 (VDDIN_1), U_AWR1.J1 (VDDIN_2), U_AWR1.V4 (VDDIN_3), U_AWR1.V6 (VIN_SRAM_2), U_AWR1.V7 (VNWA_2), U_AWR1.V8 (VDDIN_4), U_AWR1.V12 (VIN_SRAM_3), U_AWR1.V14 (VNWA_3), U_AWR1.V15 (VDDIN_5)
AWR_1V2_FB: C_AWR12_FF1.2, R_AWR12_FB1.2, R_AWR12_FB2.1, U_AWR_BUCK12.2 (FB)
AWR_1V2_SW: L_AWR_BUCK12.1, U_AWR_BUCK12.6 (SW)
AWR_1V3: C_AWR_1V3_PF_1.1, C_AWR_1V3_PF_2.1, FB_AWR_1V3.2, J_CAST_radar_module1.37 (AWR_1V3@216.541deg), R_DEV_MON3_0.1, TP_DEV_DBG_AWR_1V3.1, U_AWR1.H16 (VIN_13RF2_1), U_AWR1.H17 (VIN_13RF2_2), U_AWR1.H18 (VIN_13RF2_3), U_AWR1.J16 (VIN_13RF1_1), U_AWR1.J17 (VIN_13RF1_2), U_AWR1.J18 (VIN_13RF1_3)
AWR_1V3_BK: C_AWR13_FF1.1, C_AWR_1V3_1_1.1, C_AWR_1V3_1_2.1, C_AWR_1V3_2.1, FB_AWR_1V3.1, L_AWR_BUCK13.2, R_AWR13_FB1.1
AWR_1V3_FB: C_AWR13_FF1.2, R_AWR13_FB1.2, R_AWR13_FB2.1, U_AWR_BUCK13.C1 (FB)
AWR_1V3_SW: L_AWR_BUCK13.1, U_AWR_BUCK13.B2 (SW)
AWR_1V8: C_AWR_1V8_PF_1.1, C_AWR_1V8_PF_2.1, C_AWR_OSC_VDD1.1, FB_AWR_1V8.2, J_CAST_radar_module1.40 (AWR_1V8@235.489deg), R_DEV_MON3_1.1, TP_DEV_DBG_AWR_1V8.1, U_AWR1.A12 (VIN_18VCO_1), U_AWR1.B1 (VIOIN_18_1), U_AWR1.C11 (VIN_18VCO_2), U_AWR1.C15 (VIN_18CLK_1), U_AWR1.C18 (VIN_18CLK_2), U_AWR1.F1 (VIOIN_18_2), U_AWR1.K1 (VIOIN_18_3), U_AWR1.M16 (VIN_18BB_1), U_AWR1.M17 (VIN_18BB_2), U_AWR1.M18 (VIN_18BB_3), U_AWR1.U2 (VIOIN_18DIFF), U_AWR1.V11 (VIOIN_18_4), Y_AWR_HSE1.1 (STANDBY#), Y_AWR_HSE1.4 (VDD)
AWR_1V8_BK: C_AWR18_FF1.1, C_AWR_1V8_1_1.1, C_AWR_1V8_1_2.1, C_AWR_1V8_2.1, FB_AWR_1V8.1, L_AWR_BUCK18.2, R_AWR18_FB1.1
AWR_1V8_FB: C_AWR18_FF1.2, R_AWR18_FB1.2, R_AWR18_FB2.1, U_AWR_LDO18.2 (FB)
AWR_1V8_SW: L_AWR_BUCK18.1, U_AWR_LDO18.6 (SW)
AWR_CLKREF: R_AWR_CLK_SER1.2, R_AWR_CLK_SH1.1, U_AWR1.A7 (CLKP)
AWR_DBG_GPIO: J_CAST_radar_module1.41 (AWR_DBG_GPIO@240.902deg), TP_DEV_DBG_AWR_DBG_GPIO1.1, U_AWR1.M2 (GPIO_0)
AWR_DRDY: J_CAST_companion_compute1.29 (AWR_DRDY@110.977deg), J_CAST_radar_module1.7 (AWR_DRDY@110.977deg), R_AWR_DRDY_PU1.2, U_AWR1.B2 (SPI_HOST_INTR), U_MPU1.U8 (PF1)
AWR_FAULT: J_CAST_companion_compute1.30 (AWR_FAULT@113.684deg), J_CAST_radar_module1.8 (AWR_FAULT@113.684deg), R_AWR_FAULT_PU1.2, U_AWR1.U15 (NERROR_OUT), U_MPU1.D5 (PI7)
AWR_NERR_IN: R_AWR_NERRIN_PU1.2, U_AWR1.U14 (NERROR_IN)
AWR_NRESET: C_AWR_NRST1.1, J_CAST_companion_compute1.31 (AWR_NRESET@116.391deg), J_CAST_radar_module1.9 (AWR_NRESET@116.391deg), R_AWR_NRST1.2, U_AWR1.U11 (NRESET), U_MPU1.D4 (PI6)
AWR_OSC_OUT: R_AWR_CLK_SER1.1, Y_AWR_HSE1.3 (OUT)
AWR_QSPI_CLK: U_AWR1.H2 (QSPI_CLK), U_AWR_FLASH1.6 (SCK)
AWR_QSPI_CS: U_AWR1.J2 (QSPI_CS_N), U_AWR_FLASH1.1 (CE#)
AWR_QSPI_IO2: R_AWR_QSPI_IO2.2, U_AWR1.J3 (QSPI[2]), U_AWR_FLASH1.3 (WP#/SIO2)
AWR_QSPI_IO3: R_AWR_QSPI_IO3.2, U_AWR1.K2 (QSPI[3]), U_AWR_FLASH1.7 (RESET#/HOLD#/SIO3)
AWR_QSPI_SI: U_AWR1.H3 (QSPI[0]), U_AWR_FLASH1.5 (SI/SIO0)
AWR_QSPI_SO: U_AWR1.G2 (QSPI[1]), U_AWR_FLASH1.2 (SO/SIO1)
AWR_RS232_RX: J_CAST_companion_compute1.32 (AWR_RS232_RX@119.098deg), J_CAST_radar_module1.10 (AWR_RS232_RX@119.098deg), J_DEV_LA1.11, R_AWR_RS232_PU1.2, U_AWR1.V16 (RS232_RX), U_MPU1.L12 (PH7)
AWR_RS232_TX: J_CAST_companion_compute1.34 (AWR_RS232_TX@132.632deg), J_CAST_radar_module1.12 (AWR_RS232_TX@132.632deg), J_DEV_LA1.9, U_AWR1.U16 (RS232_TX), U_MPU1.M12 (PH8)
AWR_SOP0: J_CAST_radar_module1.38 (AWR_SOP0@224.662deg), R_AWR_SOP0.2, TP_DEV_DBG_AWR_SOP0.1, U_AWR1.U10 (TDO)
AWR_SOP1: R_AWR_SOP1.1, U_AWR1.M3 (SYNC_OUT)
AWR_SOP2: R_AWR_SOP2.1, R_AWR_SOP2_SER1.2, U_AWR1.V10 (PMIC_CLKOUT)
AWR_SOP2_CTL: J_CAST_companion_compute1.36 (AWR_SOP2_CTL@140.752deg), J_CAST_radar_module1.14 (AWR_SOP2_CTL@140.752deg), J_DEV_LA1.13, R_AWR_SOP2_SER1.1, U_MPU1.N4 (PI8)
AWR_SPI_CLK: J_CAST_companion_compute1.37 (AWR_SPI_CLK@143.459deg), J_CAST_radar_module1.15 (AWR_SPI_CLK@143.459deg), J_DEV_LA1.1, U_AWR1.D2 (SPIA_CLK), U_MPU1.B10 (PD11)
AWR_SPI_CS: J_CAST_companion_compute1.39 (AWR_SPI_CS@151.579deg), J_CAST_radar_module1.17 (AWR_SPI_CS@151.579deg), J_DEV_LA1.3, U_AWR1.C2 (SPIA_CS_N), U_MPU1.A10 (PD2)
AWR_SPI_MISO: J_CAST_companion_compute1.41 (AWR_SPI_MISO@165.113deg), J_CAST_radar_module1.19 (AWR_SPI_MISO@165.113deg), J_DEV_LA1.7, U_AWR1.D1 (SPIA_MISO), U_MPU1.A14 (PE2)
AWR_SPI_MOSI: J_CAST_companion_compute1.42 (AWR_SPI_MOSI@167.82deg), J_CAST_radar_module1.20 (AWR_SPI_MOSI@167.82deg), J_DEV_LA1.5, U_AWR1.F2 (SPIA_MOSI), U_MPU1.B14 (PE4)
AWR_TCK: J_CAST_radar_module1.39 (AWR_TCK@230.075deg), TP_DEV_DBG_AWR_TCK1.1, U_AWR1.T3 (TCK)
AWR_TDI: J_CAST_radar_module1.36 (AWR_TDI@211.128deg), TP_DEV_DBG_AWR_TDI1.1, U_AWR1.U9 (TDI)
AWR_TMS: J_CAST_radar_module1.43 (AWR_TMS@254.436deg), TP_DEV_DBG_AWR_TMS1.1, U_AWR1.U8 (TMS)
AWR_VOUT_14APLL: C_AWR_14APLL1.1, U_AWR1.A10 (VOUT_14APLL)
AWR_VOUT_14SYNTH: C_AWR_14SYNTH1.1, U_AWR1.A9 (VOUT_14SYNTH)
AWR_VOUT_PA: C_AWR_VOUT_PA1.1, C_AWR_VOUT_PA_BULK_1.1, C_AWR_VOUT_PA_BULK_2.1, C_AWR_VOUT_PA_BULK_3.1, C_AWR_VOUT_PA_BULK_4.1, C_AWR_VOUT_PA_BULK_5.1, U_AWR1.G16 (VOUT_PA_1), U_AWR1.G17 (VOUT_PA_2), U_AWR1.G18 (VOUT_PA_3)
AWR_WARM_RST: R_AWR_WARMRST_PU1.2, U_AWR1.U13 (WARM_RESET)
BAT_CELL1_POS: J_CAST_aft_end_board1.5 (BAT_CELL1_POS@29.75deg), J_CAST_power_board1.4 (BAT_CELL1_POS@29.774deg), P_CELL_WIRE_POS1.1, R_BAT1_ISO1.1
BAT_CELL2_POS: J_CAST_aft_end_board1.33 (BAT_CELL2_POS@282.25deg), J_CAST_power_board1.35 (BAT_CELL2_POS@330.226deg), P_CELL_WIRE_POS2.1, R_BAT2_ISO1.1
BAT_CELL3_POS: J_CAST_aft_end_board1.32 (BAT_CELL3_POS@279.5deg), J_CAST_power_board1.34 (BAT_CELL3_POS@327.519deg), P_CELL_WIRE_POS3.1, R_BAT3_ISO1.1
BAT_ISO_EN: Q_ISO_DRV1.1 (G), Q_ISO_EXT1.3 (D), R_ISO_EN_PD1.1, R_ISO_EN_PU1.2
BAT_ISO_EXTG: Q_ISO_EXT1.1 (G), R_ISO_EXT_H1.2, R_ISO_EXT_L1.1
BAT_ISO_G: Q_ISO1.3 (G), R_ISO_H1.2, R_ISO_L1.1
BAT_ISO_GD: Q_ISO_DRV1.3 (D), R_ISO_L1.2
BAT_PROT: CBAT1_1.1, CBAT1_2.1, CBAT1_3.1, CBAT1_4.1, CBAT2_1.1, CBAT2_2.1, CBAT2_3.1, CBAT2_4.1, CBAT3.1, J_CAST_power_board1.1 (BAT_PROT@0deg), QMAIN1.4 (S_1), QMAIN1.8 (S_2), Q_ISO1.4 (S_1), Q_ISO1.8 (S_2), R_DEV_SH_BAT_PROT_ACT1.2, R_DEV_SH_BAT_PROT_AFT1.2, R_DEV_SH_BAT_PROT_CAM1.2, R_DEV_SH_BAT_PROT_QPD1.2, R_DEV_SH_BAT_PROT_RADAR1.2, R_DEV_SH_BAT_PROT_WAKE1.2, R_ISO_H1.1, TP_DEV_SH_BAT_PROT_AFT_B1.1, TP_DEV_SH_BAT_PROT_CAM_B1.1, TP_DEV_SH_BAT_PROT_QPD_B1.1
BAT_PROT__ACT: C_HEALTH_COIL_1.1, C_HEALTH_COIL_2.1, C_HEALTH_COIL_3.1, C_HEALTH_COIL_4.1, C_HEALTH_COIL_5.1, D_EXT_IN1.1 (K), D_HEALTH_COIL1.1 (K), J_CAST_activation_interface1.1 (BAT_PROT@0deg), R_DEV_SH_BAT_PROT_ACT1.1
BAT_PROT__AFT: J_CAST_aft_end_board1.44 (BAT_PROT@336.25deg), L_HEALTH_COIL1.1 (FEED), R_DEV_SH_BAT_PROT_AFT1.1, TP_DEV_SH_BAT_PROT_AFT_T1.1
BAT_PROT__CAM: C_CAM_BUCK_IN1.1, C_CAM_LDO_VAA_IN1.1, C_IR_TX_C1.1, D_IR_TX_C1.2 (A), J_CAST_camera_module1.1 (BAT_PROT@0deg), R_DEV_SH_BAT_PROT_CAM1.1, TP_DEV_SH_BAT_PROT_CAM_T1.1, U_CAM_BUCK_VCORE1.7 (VIN), U_CAM_LDO_VAA1.1 (IN), U_CAM_LDO_VAA1.3 (EN)
BAT_PROT__QPD: C_IR_TX_Q1.1, D_IR_TX_Q1.2 (A), J_CAST_qpd_module1.1 (BAT_PROT@0deg), R_DEV_SH_BAT_PROT_QPD1.1, TP_DEV_SH_BAT_PROT_QPD_T1.1
BAT_PROT__RADAR: C_AWR_BUCK_IN1_1.1, C_AWR_BUCK_IN1_2.1, C_AWR_BUCK_IN1_3.1, C_AWR_BUCK_IN1_4.1, C_AWR_BUCK_IN1_5.1, C_AWR_BUCK_IN2.1, C_AWR_BUCK_IN3_1.1, C_AWR_BUCK_IN3_2.1, C_AWR_BUCK_IN3_3.1, C_AWR_BUCK_IN3_4.1, C_AWR_BUCK_IN3_5.1, C_IR_TX1.1, D_IR_TX1.2 (A), J_CAST_radar_module1.1 (BAT_PROT@0deg), R_DEV_SH_BAT_PROT_RADAR1.1, U_AWR_BUCK12.7 (VIN), U_AWR_BUCK13.A2 (VIN), U_AWR_LDO18.7 (VIN)
BAT_PROT__WAKE: J_CAST_wakeup_board1.1 (BAT_PROT@0deg), R_DEV_SH_BAT_PROT_WAKE1.1, TP_BAT1.1
BAT_RAW: C_AON_IN1.1, C_BAT_BULK1.1, C_BAT_BULK2.1, C_BAT_BULK3.1, C_BAT_BULK4.1, C_BAT_BULK5.1, C_BAT_BULK6.1, C_DEV_FLAT_PWR_SS1.2, J_CAST_activation_interface1.14 (BAT_RAW@56.842deg), J_CAST_power_board1.8 (BAT_RAW@56.842deg), J_CAST_wakeup_board1.7 (BAT_RAW@56.842deg), Q_AON_EN1.2 (S), Q_DEV_FLAT_PWR1.1 (D_1), Q_DEV_FLAT_PWR1.2 (D_2), Q_DEV_FLAT_PWR1.5 (D_3), Q_DEV_FLAT_PWR1.6 (D_4), Q_DEV_FLAT_PWR1.7 (D_5), Q_ISO1.1 (D_1), Q_ISO1.2 (D_2), Q_ISO1.5 (D_3), Q_ISO1.6 (D_4), Q_ISO1.7 (D_5), RAON_PU1.1, RMAIN_PU1.1, R_BAT1_ISO1.2, R_BAT2_ISO1.2, R_BAT3_ISO1.2, R_DEV_LED_FLAT1.1, R_JUMP_PU1.1, U_AON_LDO1.4 (VIN), U_TMR_LDO1.3 (ON/OFF), U_TMR_LDO1.4 (VIN)
BAT_SENSE: C_BAT_SENSE1.1, R_BAT_SENSE_H1.2, R_BAT_SENSE_L1.1, U_WBA1.G2 (PA3)
BLE_ANT: C_BLE_DCBLK1.2, U_ANTSW_S1.3 (RF1)
BLE_RF: C_BLE_DCBLK1.1, C_WBA_PI2.1, L_WBA_PI1.2
BOOT0: J_CAST_aft_end_board1.42 (BOOT0@327deg), J_CAST_companion_compute1.79 (BOOT0@354.586deg), J_DEV_FLAT_IO1.1, R_ESD_MPU_BOOT0.1, R_MPU_BOOT0.2, U_DEV_FLATSW3.3 (1B), U_ESD_AFT1.1 (IO1)
BOOT0__MPU: R_ESD_MPU_BOOT0.2, U_MPU1.T2 (BOOT0), U_MPU1.T3 (BOOT2)
CAM_CPNEG: C_CAM_CPNEG1.1, U_CAM1.A4 (CPNEG_OUT), U_CAM1.A5 (CPNEG_IN)
CAM_CPPOS: C_CAM_CPPOS1.1, U_CAM1.B9 (CPPOS_OUT), U_CAM1.C9 (CPPOS_IN)
CAM_CSI_CLK_N: J_CAST_camera_module1.9 (CAM_CSI_CLK_N@170.526deg), J_CAST_companion_compute1.43 (CAM_CSI_CLK_N@170.526deg), J_CAST_radar_module1.21 (CAM_CSI_CLK_N@170.526deg), U_CAM1.K4 (CLKN), U_MPU1.C2 (CSI_CKN)
CAM_CSI_CLK_P: J_CAST_camera_module1.10 (CAM_CSI_CLK_P@173.233deg), J_CAST_companion_compute1.44 (CAM_CSI_CLK_P@173.233deg), J_CAST_radar_module1.22 (CAM_CSI_CLK_P@173.233deg), U_CAM1.K5 (CLKP), U_MPU1.C1 (CSI_CKP)
CAM_CSI_D0_N: J_CAST_camera_module1.11 (CAM_CSI_D0_N@175.94deg), J_CAST_companion_compute1.45 (CAM_CSI_D0_N@175.94deg), J_CAST_radar_module1.23 (CAM_CSI_D0_N@175.94deg), U_CAM1.J6 (DATA1N), U_MPU1.E1 (CSI_D0N)
CAM_CSI_D0_P: J_CAST_camera_module1.12 (CAM_CSI_D0_P@178.647deg), J_CAST_companion_compute1.46 (CAM_CSI_D0_P@178.647deg), J_CAST_radar_module1.24 (CAM_CSI_D0_P@178.647deg), U_CAM1.J7 (DATA1P), U_MPU1.E2 (CSI_D0P)
CAM_CSI_D1_N: J_CAST_camera_module1.13 (CAM_CSI_D1_N@181.353deg), J_CAST_companion_compute1.47 (CAM_CSI_D1_N@181.353deg), J_CAST_radar_module1.25 (CAM_CSI_D1_N@181.353deg), U_CAM1.J2 (DATA2N), U_MPU1.D2 (CSI_D1N)
CAM_CSI_D1_P: J_CAST_camera_module1.14 (CAM_CSI_D1_P@184.06deg), J_CAST_companion_compute1.48 (CAM_CSI_D1_P@184.06deg), J_CAST_radar_module1.26 (CAM_CSI_D1_P@184.06deg), U_CAM1.J3 (DATA2P), U_MPU1.D1 (CSI_D1P)
CAM_EXTCLK: U_CAM1.J9 (EXTCLK), Y_CAM_EXTCLK1.3 (OUT)
CAM_LDO2V4: C_CAM_LDO2V4.1, U_CAM1.H4 (LDO2V4)
CAM_NRST: J_CAST_camera_module1.15 (CAM_NRST@186.767deg), J_CAST_companion_compute1.49 (CAM_NRST@186.767deg), J_CAST_radar_module1.27 (CAM_NRST@186.767deg), R_CAM_NRST_PU1.2, U_CAM1.H1 (RESETN), U_MPU1.K12 (PA9)
CAM_SCL: Q_CAM_SCL1.2 (S), R_CAM_SCL_PU1.2, U_CAM1.B1 (SCL)
CAM_SDA: Q_CAM_SDA1.2 (S), R_CAM_SDA_PU1.2, U_CAM1.C1 (SDA)
CAM_VAA_2V8: C_CAM_LDO_VAA_OUT_1.1, C_CAM_LDO_VAA_OUT_2.1, C_CAM_VAA_1.1, C_CAM_VAA_BULK1.1, R_CAM_VAA_SRC1.2, U_CAM1.C4 (VANA_1), U_CAM1.C5 (VANA_2), U_CAM1.C6 (VANA_3), U_CAM1.C7 (VANA_4), U_CAM1.C8 (VANA_5), U_CAM1.D7 (VANA_6), U_CAM1.D8 (VANA_7), U_CAM1.H5 (VANA_8), U_CAM_LDO_VAA1.5 (OUT)
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
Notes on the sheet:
activation_interface
Rail decoupling - no pin declared
aft_end_board
camera_module
companion_compute
dev_board
dev_diag
power_board
qpd_module
radar_module
wakeup_board

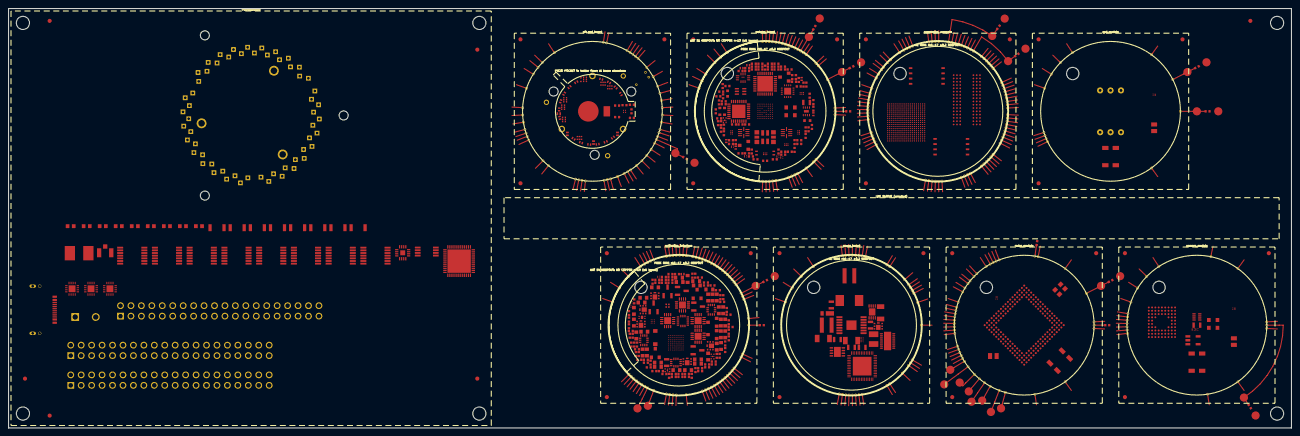
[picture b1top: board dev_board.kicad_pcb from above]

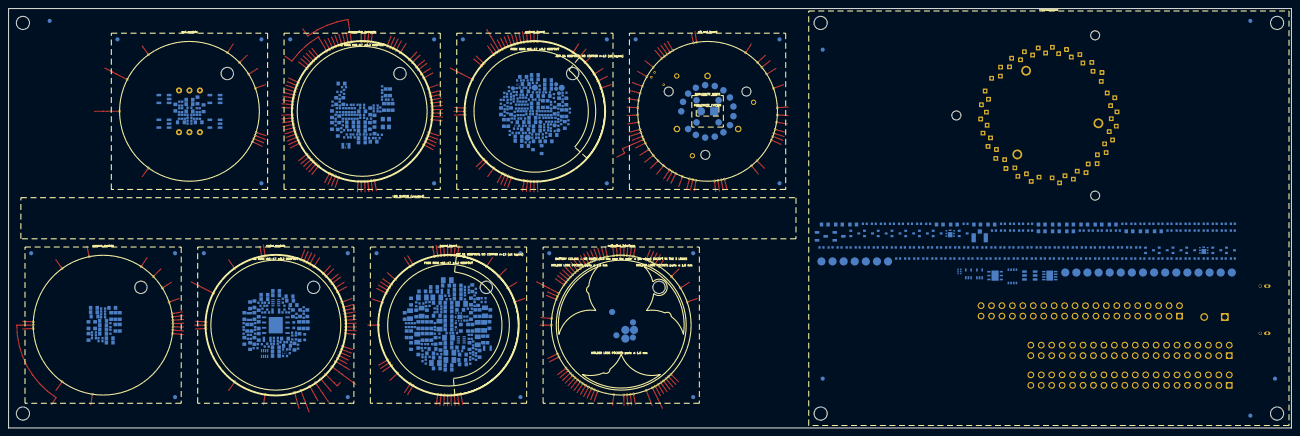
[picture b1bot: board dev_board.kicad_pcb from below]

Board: 8 copper layers, 312.0 x 102.0 mm, 1248 parts (724 on the bottom side), 680 nets.

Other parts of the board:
FID1, FID2, FID3, FID4, FID5, FID6: fiducial
FID_activation_interface_B1, FID_activation_interface_B2, FID_activation_interface_B3: fiducial
FID_activation_interface_T1, FID_activation_interface_T2, FID_activation_interface_T3: fiducial
FID_aft_end_board_B1, FID_aft_end_board_B2, FID_aft_end_board_B3: fiducial
FID_aft_end_board_T1, FID_aft_end_board_T2, FID_aft_end_board_T3: fiducial
FID_camera_module_B1, FID_camera_module_B2, FID_camera_module_B3: fiducial
FID_camera_module_T1, FID_camera_module_T2, FID_camera_module_T3: fiducial
FID_companion_compute_B1, FID_companion_compute_B2, FID_companion_compute_B3: fiducial
FID_companion_compute_T1, FID_companion_compute_T2, FID_companion_compute_T3: fiducial
FID_power_board_B1, FID_power_board_B2, FID_power_board_B3: fiducial
FID_power_board_T1, FID_power_board_T2, FID_power_board_T3: fiducial
FID_programmer_B1, FID_programmer_B2, FID_programmer_B3: fiducial
FID_programmer_T1, FID_programmer_T2, FID_programmer_T3: fiducial
FID_qpd_module_B1, FID_qpd_module_B2, FID_qpd_module_B3: fiducial
FID_qpd_module_T1, FID_qpd_module_T2, FID_qpd_module_T3: fiducial
FID_radar_module_B1, FID_radar_module_B2, FID_radar_module_B3: fiducial
FID_radar_module_T1, FID_radar_module_T2, FID_radar_module_T3: fiducial
FID_wakeup_board_B1, FID_wakeup_board_B2, FID_wakeup_board_B3: fiducial
FID_wakeup_board_T1, FID_wakeup_board_T2, FID_wakeup_board_T3: fiducial
MH1, MH2, MH3, MH4, MH5, MH6: smash_mech_mount
MH7, MH8, MH9: smash_mech_aft_end_board_aft_cap_screw
MH10: smash_mech_activation_interface_potting
MH11: smash_mech_wakeup_board_potting
MH12: smash_mech_power_board_potting
MH13: smash_mech_companion_compute_potting
MH14: smash_mech_radar_module_potting
MH15: smash_mech_qpd_module_potting
MH16: smash_mech_camera_module_potting
MH17, MH18, MH19: smash_mech_fixture_collar
